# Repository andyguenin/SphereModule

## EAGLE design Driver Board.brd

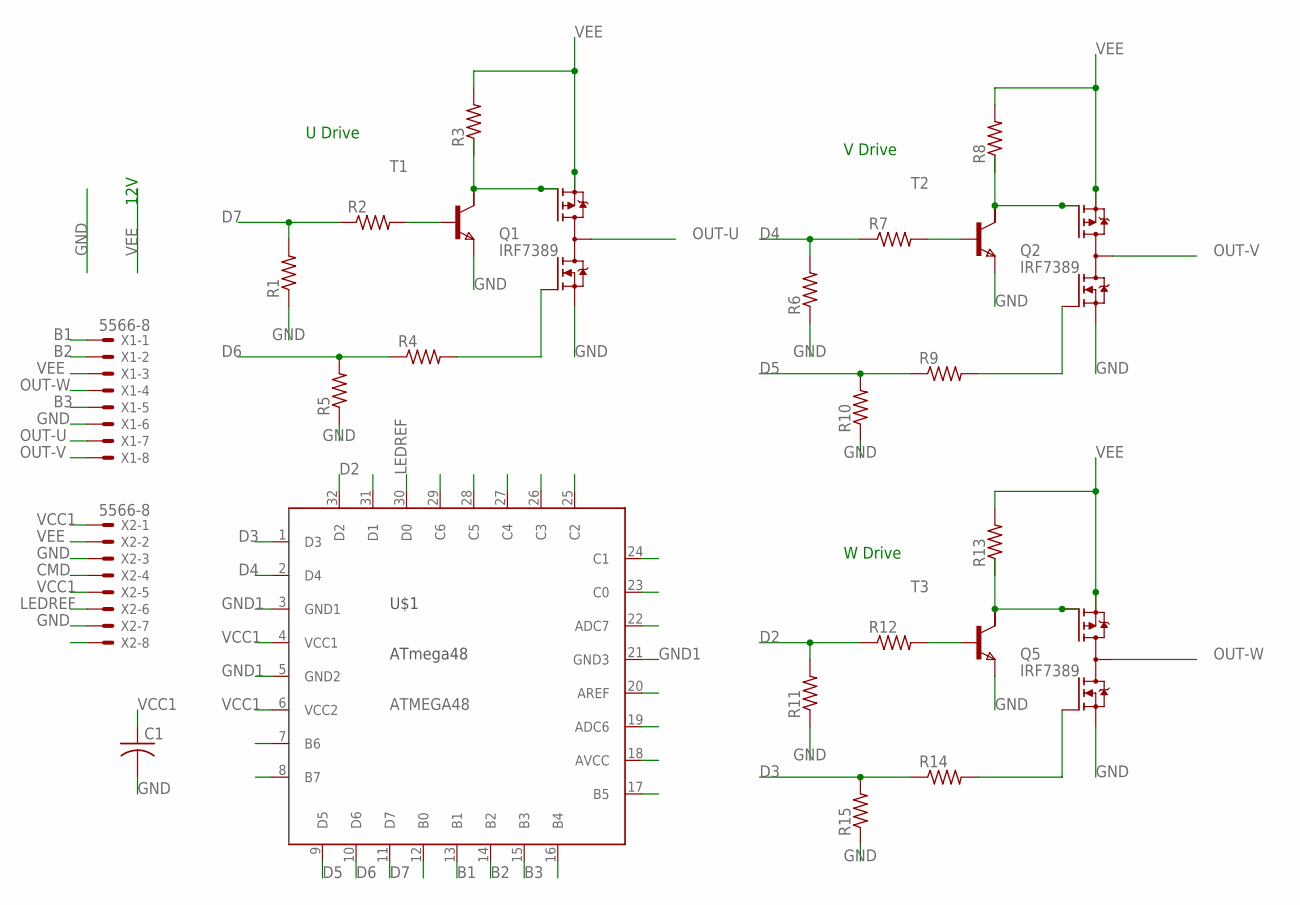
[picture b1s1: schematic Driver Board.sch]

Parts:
C1: C-USC1206; C1206
Q1, Q2, Q5: IRF7389; SO08-IRF
R1, R2, R3, R4, R5, R6, R7, R8, R9, R10, R11, R12, R13, R14, R15: R-US_R1206; R1206
T1, T2, T3: NPNSOT223; SOT223
U$1: ATMEGA48
X1, X2: 5566-8

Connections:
B1: U$1.13 (B1), X1.1
B2: U$1.14 (B2), X1.2
B3: U$1.15 (B3), X1.5
CMD: X2.4
D2: R11.2, R12.1, U$1.32 (D2)
D3: R14.1, R15.2, U$1.1 (D3)
D4: R6.2, R7.1, U$1.2 (D4)
D5: R9.1, R10.2, U$1.9 (D5)
D6: R4.1, R5.2, U$1.10 (D6)
D7: R1.2, R2.1, U$1.11 (D7)
GND: C1.2, Q1.1 (N-S), Q2.1 (N-S), Q5.1 (N-S), R1.1, R5.1, R6.1, R10.1, R11.1, R15.1, T1.3 (E), T2.3 (E), T3.3 (E), X1.6, X2.3, X2.7
GND1: U$1.3 (GND1), U$1.5 (GND2), U$1.21 (GND3)
LEDREF: U$1.30 (D0), X2.6
unnamed: Q1.4 (P-G), T1.2 (C1)
unnamed: Q2.4 (P-G), T2.2 (C1)
unnamed: R2.2, T1.1 (B)
unnamed: R7.2, T2.1 (B)
unnamed: Q1.2 (N-G), R4.2
unnamed: Q2.2 (N-G), R9.2
unnamed: Q5.4 (P-G), T3.2 (C1)
unnamed: R12.2, T3.1 (B)
unnamed: Q5.2 (N-G), R14.2
OUT-U: Q1.5 (D), Q1.6 (D), Q1.7 (D), Q1.8 (D), X1.7
OUT-V: Q2.5 (D), Q2.6 (D), Q2.7 (D), Q2.8 (D), X1.8
OUT-W: Q5.5 (D), Q5.6 (D), Q5.7 (D), Q5.8 (D), X1.4
VCC1: C1.1, U$1.4 (VCC1), U$1.6 (VCC2), X2.1, X2.5
VEE: Q1.3 (P-S), Q2.3 (P-S), Q5.3 (P-S), R3.2, R8.2, R13.2, X1.3, X2.2

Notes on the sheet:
12V
U Drive
V Drive
W Drive

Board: 2 copper layers, 25 parts (0 on the bottom side), 26 nets, no tracks yet.

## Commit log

2012-02-21 Created the schema for ATMega48 driver board
2012-02-22 Updated the schematic and started the board.`
2012-03-22 im a muthafucking commit
